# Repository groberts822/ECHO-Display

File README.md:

# ECHO-Display
ECHO, or Embedded Controller &amp; Hidden Operations. Music display by day, game console by night.
To begin, I started working on my schematic. It was quite simple, I chose to 2 1x7 headers instead of going through the pain to spend forever searching through the internet for the right symbol and footprint of the esp32. 
I prefer to use net labels, especially with schematics that are this simple, so here's my schematic below:

In addition, my PCB was quite simple, however it took some measurements, where I used the provided STEP files and just measured the necessary sizes in fusion. 
The 1x7 headers for the ESP32 ARE spaced out correctly (Again, made sure by measuring the part in fusion), and I made sure the display had enough space so it wouldnt cover the switches. I also chose to do the esp32 on the back side, the display ontop, and the switches lined up below the display. I also added mounting holes and added a custom logo to my pcb just for fun (and mounting holes for mounting to case). Below is the PCB: 

In addition, I used the provided STEP files to make the 3D viewer. Just a note, the DIsplay does not have headers in this 3D viewer, because they are specially spaced pins (3mm apart not 2.54mm), so I will have 
to use the header pins which come with the display itself. I also made sure to adjust the footprint so that it was actually 3mm apart and would work. Below is the 3D model: 

Backside: 

Next I saved the STEP for the board with the parts, and moved on over to fusion. I utilized the mounting holes and provided holes on each side of it, so I can use heat-set inserts on the bottom half, and then use screws to secure the top half and pcb into place. I chose to go with somewhat of a unique spotify display design, as I made it so the display was sideways and ontop, then the 3 switches below it, and it was like a stand proped up almost in the shape of an iphone holder. Below are some images of the 3D model: 

I would like to note, there are holes for heat-press inserts, which I have myself, alongside the proper screws, so unless it comes in the kit for this starter project, I dont need them hence why they aren't separately mentioned in the BOM. 

After basically finishing the whole 3D modelling and such, I worked on the firmware, where although I cannot put here, I provided a snippet of the code below, with the full thing being in the github repo:

BOM is below:

| Qty | Part | Link | Notes |
|-----|------|------|-------|
| 1 | ESP32 LOLIN C3 Mini | [AliExpress](https://www.aliexpress.us/item/3256804553736450.html?pdp_npi=4%40dis%21USD%21US%20%245.47%21US%20%240.99%21%21%215.47%210.99%21%402103119417736152975654869d1287%2112000056120453300%21sh%21US%217425461850%21X&spm=a2g0o.store_pc_home.productList_2009695634908.1005004740051202&gatewayAdapt=glo2usa) | |
| 1 | 1.8" TFT Display ST7735 | [AliExpress](https://www.aliexpress.us/item/3256809750593574.html?spm=a2g0o.productlist.main.2.71184dab1tsmCB&algo_pvid=4540c901-2267-4297-894a-94d7b7e40b90&algo_exp_id=4540c901-2267-4297-894a-94d7b7e40b90-1&pdp_ext_f=%7B"order"%3A"199"%2C"eval"%3A"1"%2C"fromPage"%3A"search"%7D&pdp_npi=6%40dis%21USD%218.14%210.99%21%21%2155.72%216.76%21%40210311cc17736153139033443ee5db%2112000050625051194%21sea%21US%217425461850%21ABX%211%210%21n_tag%3A-29910%3Bd%3A6670291b%3Bm03_new_user%3A-29895%3BpisId%3A5000000197847475&curPageLogUid=sl2faarfQKwY&utparam-url=scene%3Asearch%7Cquery_from%3A%7Cx_object_id%3A1005009936908326%7C_p_origin_prod%3A&_gl=1*4nhmo6*_gcl_au*OTExMzQxMzAyLjE3NzM2MTUyNjg.*_ga*MTY2NjQwMzk4OC4xNzczNjE1MjY4*_ga_VED1YSGNC7*czE3NzM2MTUyNjgkbzEkZzEkdDE3NzM2MTUzMTIkajE2JGwwJGgw) | |
| 1 | Custom PCB | [JLCPCB](https://jlcpcb.com) | Already ordered |
| 3 | Cherry MX Switches | [NovelKeys](https://novelkeys.com/products/cherry-mx2a-switches) | Leftover from Hackpad |
| 3 | Keycaps (1u) | [NovelKeys](https://novelkeys.com) | Leftover from Hackpad |
| 4 | M3 Heatset Inserts | [Amazon](https://www.amazon.com/initeq-M3-0-5-Threaded-Inserts-Printing/dp/B077CJV3Z9) | Leftover from Hackpad |
| 4 | M3 Screws | [Amazon](https://www.amazon.com/s?k=m3+screws) | Leftover from Hackpad |

All files have been uploaded to the github repo, and just to be sure I had also provided the gerber files so its easier to just take them straight off of there when I order the pcb. 
Lastly, ECHO, or Embedded Controller & Hidden Operations (yes I know the name is weird, it'll make sense), is a desk Spotify display built using an ESP32 C3 Mini, alongside a 1.8" TFT screen, 3 mechanical switches for playback control, and a hidden Space Invaders game unlocked by holding all 3 keys (hence the "& Hidden Operations").
The display shows your current track with mood-based colors, scrolling text, animated bars, and a progress bar. The PCB was (although as expected) built in KiCad while the case was designed around the full PCB in Fusion360. 
The project includes a Case folder with CAD files, a PCB folder with all KiCad and manufacturing files, and Firmware folder with the Arduino firmware. 
I would also like to point out. The PCB was not needed for this project, however, I am still working on my PCB designing skills so I could use the challenge. Also, the firmware provided is NOT the final version, as I can only really finish it once I have the ESP32 and know its IP. 

Thanks for checking out ECHO. And don't forget to hold all 3 keys. 

Github Repo Link: 
https://github.com/groberts822/ECHO-Display

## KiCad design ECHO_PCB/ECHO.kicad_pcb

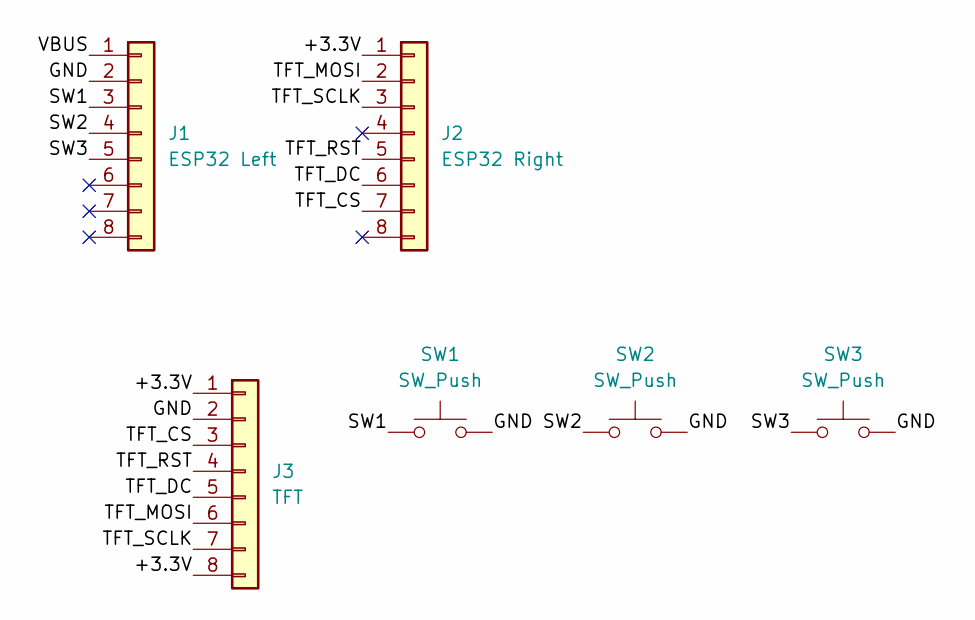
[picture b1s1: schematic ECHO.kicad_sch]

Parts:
J1: ESP32 Left; PinSocket_1x08_P2.54mm_Vertical
J2: ESP32 Right; PinSocket_1x08_P2.54mm_Vertical
J3: TFT; PinSocket_1x08_P2.54mm_Vertical
SW1, SW2, SW3: SW_Push; SW_Cherry_MX_1.00u_PCB

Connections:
/+3.3V: J2.1, J3.1, J3.8
/GND: J1.2, J3.2, SW1.2, SW2.2, SW3.2
/SW1: J1.3, SW1.1
/SW2: J1.4, SW2.1
/SW3: J1.5, SW3.1
/TFT_CS: J2.7, J3.3
/TFT_DC: J2.6, J3.5
/TFT_MOSI: J2.2, J3.6
/TFT_RST: J2.5, J3.4
/TFT_SCLK: J2.3, J3.7
/VBUS: J1.1

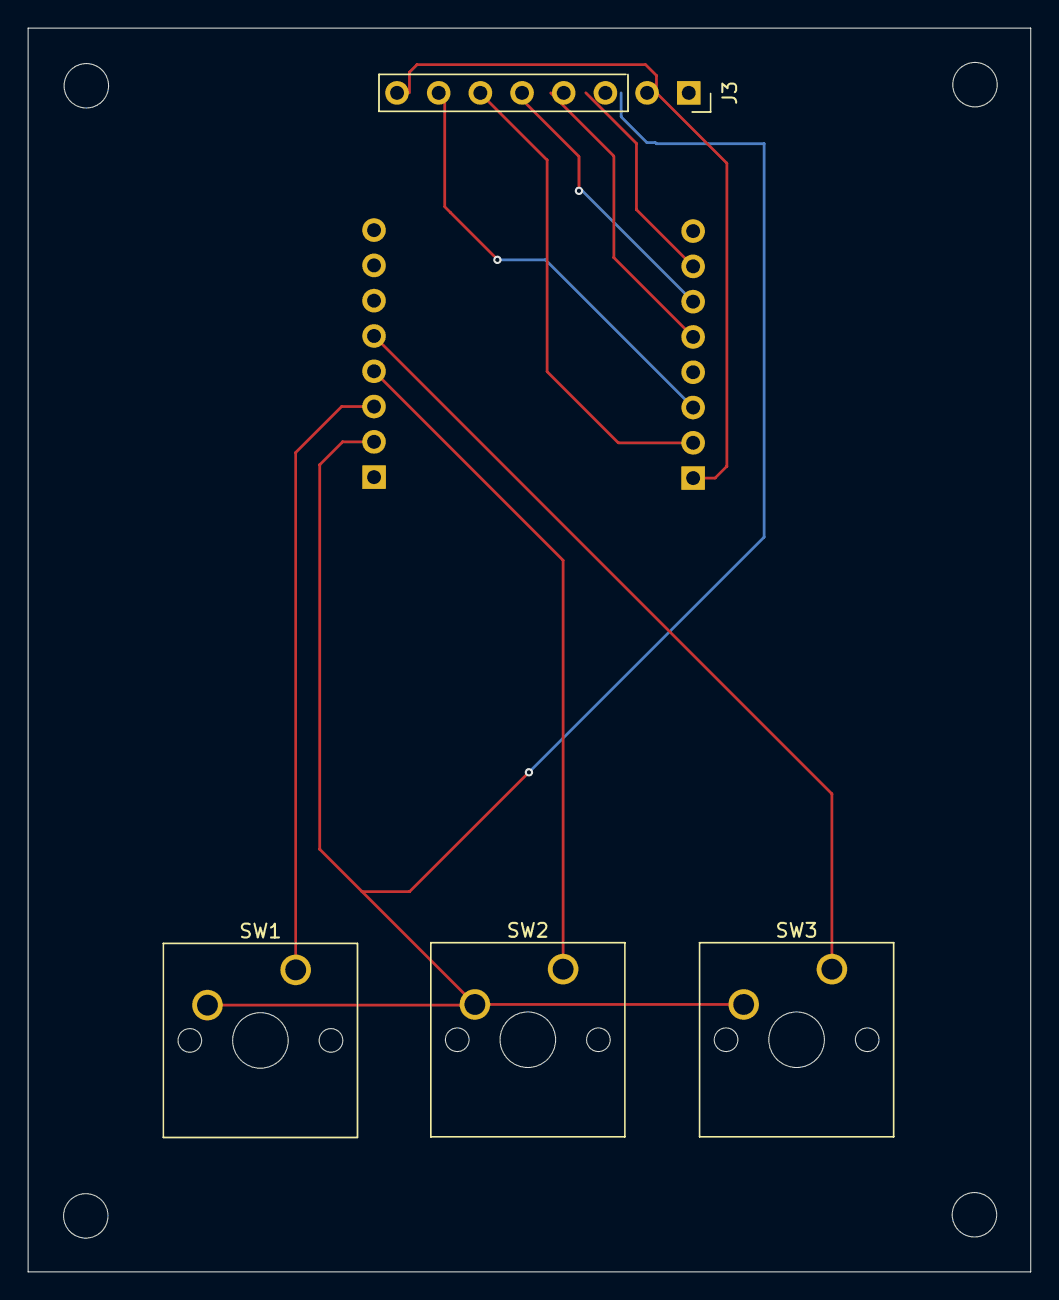
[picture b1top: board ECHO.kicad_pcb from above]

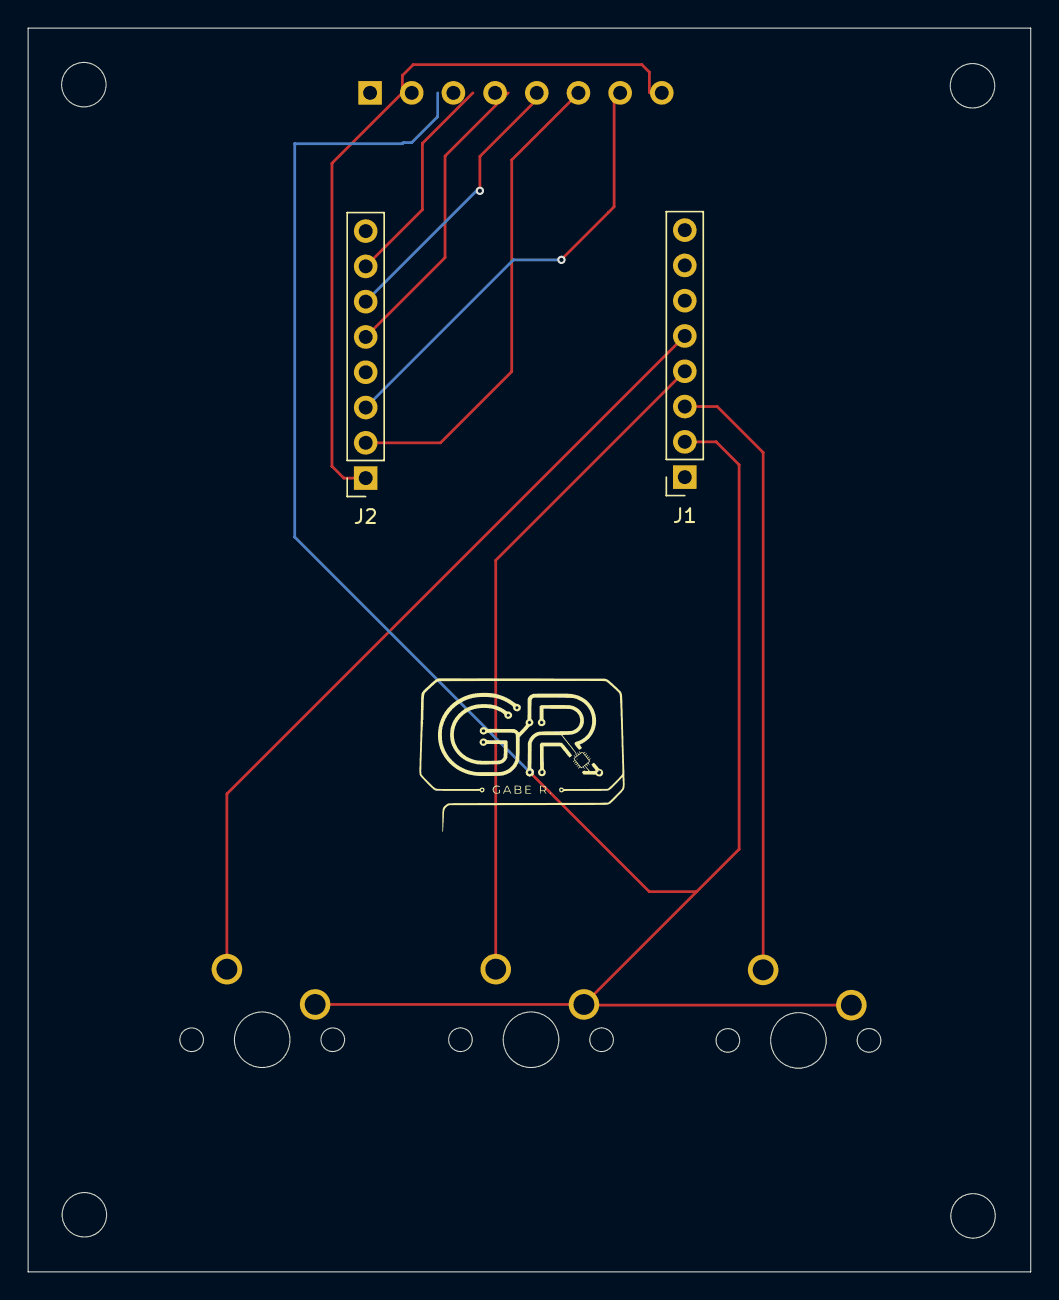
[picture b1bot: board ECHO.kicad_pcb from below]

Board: 2 copper layers, 72.2 x 89.5 mm, 6 parts (2 on the bottom side), 10 nets.

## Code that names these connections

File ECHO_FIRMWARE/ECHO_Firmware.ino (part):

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const char* CLID  = "My Spotify Client ID";
const char* CLSEC = "My Spotify Client Secret";

#define TFT_CS    3
#define TFT_RST   1
#define TFT_DC    2
#define TFT_SCLK  4
#define TFT_MOSI  5

#define BTN_L  6
#define BTN_M  7
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
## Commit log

2026-03-10 Rename ECHO.f3d to ECHO Case.f3d
